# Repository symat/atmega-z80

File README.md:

ATMega-Z80
==========

We are building here yet another 8bit hobby computer. Because it is fun. And this is what an engineer does, *"MIDWAY upon the journey of our life"*. ;)

Disclaimer: **Use anything in this repo with caution!**

Nothing works yet, we just started to plan the whole thing. The only thing we are sure is that things will change, as we move forward. Plus the fact that we will move forward very slooowly, as this is only a hobby project and everyone is quite busy with other things. 

Table of Contents
-----------------

  * [Goals](#goals)
  * [Hardware design](#hardware-design)
    * [Schema](#schema)
    * [PCB](#pcb)
  * [Using the board](#using-the-board)
  * [Development](#development)
    * [Prerequisites for Linux](#prerequisites-for-linux)
    * [Prerequisites for Windows](#prerequisites-for-windows)
    * [Prerequisites for Mac](#prerequisites-for-mac)
    * [(Optional) Configuring USB HWID](#optional-configuring-usb-hwid)
	* [ATMega Programmer](#atmega-programmer)
	  * [Initializing ATMega clock](#initializing-atmega-clock)
	  * [Deploying the ATMega code](#deploying-the-atmega-code)
	* [Deploying the Z80 'ROM' code](#deploying-the-z80-rom-code)
  * [License](#license)

Goals
=====

**The main goals are:**

 - Using a well-known 8bit CPU.
 - Let's keep the HW design relatively simple. (I'm personally more interested in the 8bit programming part and want to go deeper into the kernel and user code.)
 - We should be able to compile C code to run it on the new computer.
 - We don't need a full-fledged, stand-alone computer. I'm sure everyone has already a few of those on our desks... We don't build this to actually use it for work or gaming.
 - The whole computer should not have more than a handful of ICs. No FPGA or complex MCU with a need for an expensive programmer. Anyone should be able to build it on a breadboard for $40-50 worth of components (incl. programmer). 
 - Don't use logic level (voltage) converters, keep everything e.g. on 5V or on 3.3V.
 - We can have VGA / keyboard / SD Card support later (if someone needs it), but the first thing is to have USB support and connection to a PC, so we can implement a small thin terminal program that can send keyboard and mouse events, display video, play music even.

Hardware design
===============

The basic design is not new or original, it is very much based on other projects available on the internet. I'm especially grateful for [this one, the MBC2 project](https://hackaday.io/project/159973-z80-mbc2-a-4-ics-homebrew-z80-computer) (80% of the HW design comes from this project). 

 - We use a relatively new Z80 CPU, capable to run at 10MHz.
 - A 20MHz ATMega chip (similar to those you can find in Arduino boards) is helping the CPU as ROM emulator, boot loader and clock generator. Also handling all the IO requests from the CPU.
 - An IO wait logic is implemented using an SR latch, forcing the CPU to wait until the ATMega chip processed the IO operations.
 - The ATMgega chip can access both the data bus and the first 4 bits of the address bus. Having access to a part of the address bus makes the boot loading easier and also enables us to use IO and interrupt addresses.
 - For now, we added 512 KB RAM, using 16 KB banks. The CPU will be able to set the bank ID with an IO write operation and then the given 16 KB bank will be visible for the CPU on the third 16KB memory slot of the 64KB address space (between 0x8000 and 0xbfff).
 - We store the bank address in an 8 bit gated D latch IC. This means we can address the banks in 8 bits, so the design works until 4 MB (16KB * 256). But 4MB sounds a bit overkill and also more expensive. It is hard to find a single DIP parallel 8bit SRAM chip over 512 KB. Moving away from DIP makes it harder to assemble the computer on a breadboard, while using many separate 512 KB RAM chips would require a bit more complex banking logic (with lot more footprint and wiring on the breadboard). But in theory we can extend the RAM later easily if needed.
 - We have an USB controller chip, converting the UART port of ATMega to USB.
 - The USB port is used also for powering the whole atmega-z80.
 - We have a user button and LED, both can be used by the programmer to interact directly with the user. (who needs 101 keys and zillion pixels... :p)
 - We plan to add some status indicator LEDs:
	 - Power LED (power come through the USB cable)
	 - Z80 running LED (means the Z80 is active, not in 'halt' state)
	 - USB IO LED (ATMega is communicating through the USB)
	 - CPU IO LED (the CPU is doing IO read or write)
	 - Memory LED (the CPU is reading from / writing to anywhere in the RAM)
	 - Extended memory LED (the CPU is reading from / writing to the banked part of the RAM)
	 - User LED (some program running on the Z80 turned the user LED on)

Schema
------
Please take a look here for the latest version: [schema/atmega-z80.pdf](schema/atmega-z80.pdf)

You can find the editable files in the ['schema' folder](schema/). We use the KICad tool for schema design: https://www.kicad.org/download/

PCB
---

TODO

Using the board
===============

For now, you can only interact with the board using the console application. Later we might add keyboard and display support as well as other periferias. But the console app should be always capable to emulate these, as people might not want to use dedicated periferias for ATMega-Z80.

Prerequisites to use the console:
```
pip3 install pyserial==3.5
```

Using the console:
```
src/console/console.py
```

Development
===========

The source code needs to be deployed into the ATMega chip can be found here: ['src/atmega' folder](src/atmega/)

The source code running on the Z80 can be found here: ['src/z80' folder](src/z80/)

The source code for the console app (running on the PC and connecting to the ATMega on USB): ['src/console' folder](src/z80/)

The console is mainly developed for end users, to interact with the ATMega (until we don't have keyboard and display support, or if the user don't want to buy/attch separate devices to the board). However, during development you can also use the console as a debugger and you can also upload Z80 code using the console. However, to deploy code running on the ATMega, you need to use a programmer (see: [here](#atmega-programmer) )

You can not use the console and the ATMega programmer in the same time. **Make sure you are disconnecting the USB port while you are using the programmer!**

Prerequisites for Linux
-----------------------

TODO

Prerequisites for Windows
-----------------------

TODO

Prerequisites for Mac
---------------------

First, make sure you have xcode command line developer tools installed with:
```
$ xcode-select --install
```

Then install the latest versions of the avr command line tools (avr-libc included in avr-gcc):
```
$ brew tap osx-cross/avr
$ brew install avr-gcc@11 avr-binutils avrdude
```
(you can check the current versions of avr-gcc available through homebrew here: https://github.com/osx-cross/homebrew-avr)

Add the following two lines to your .bash_profile or .zshrc file:
```
export PATH="/usr/local/opt/avr-gcc@11/bin:$PATH"
export AVRGCC_LDFLAGS="-L/usr/local/opt/avr-gcc@11/lib"
```

(Optional) Configuring USB HWID
-------------------------------

You can program the MCP2221A chip, setting the HWID (Vendor ID: 0x1209, Product ID: 0x80A0) of the USB device. We 'registered' an open USB HWID in [pid.codes](https://pid.codes/). This is not mandatory, you can also use the MCP2221A chip with factory default HWID, but in this case the console won't auto-detect the port and you need to select the correct port manually from a list each time you start the console.

**Prerequisites (python):**

```
pip3 install mcp2221==1.0.0
pip3 install hidapi==0.10.1
```

**Prerequisites (C lib):**

The mcp2221 python library is using the hidapi library, which got merged into libusb in 2019. So depending on the age of your OS, you might need to install libhidapi or libusb. 

For me on Mac with up-to-date homebrew, this worked: `brew install hidapi`

According to the project page (https://github.com/trezor/cython-hidapi) for linux this one should work at the moment:
`sudo apt-get install python-dev libusb-1.0-0-dev libudev-dev`

**Setting the HWID for the board**

Use the following command to set the Vendor ID, Product ID and Product Description on the board: `./src/console/program_hwid.py`

**Reseting the HWID**

Use the following command to reset the Vendor ID, Product ID and Product Description on the board to the MPC2221A factory defaults:  `./src/console/program_hwid.py --reset`

ATMega Programmer
-----------------

To update the code running on the ATMega, we are using the open source UABAsp programmer (https://www.fischl.de/usbasp/). It comes with an ISP 10 connector. You need to connect the programmer to the ATMega ports indicated in the schema (RESET and PB3, PB6, PB7). Also you need to connect the 5V and GND from the programmer to the board, basically using the Programmer as a power source while you are programing the board. You can not use the console and the ATMega programmer in the same time. **Make sure you are disconnecting the USB port while you are using the programmer!**

The following photo shows how to connect the ISP 10 connector to your breadboard:

### Initializing ATMega clock

ATMega shipped with internal 8MHz clock enabled and the clock prescaler set to 8, resulting in 1 MHz clock speed. In the code we assume you wired the 20 MHz crystal to ATMega already. To configure the external crystal oscillator to be used, you need to set the fuses on ATMega once before programming it. (useful online fuse bit calculator: http://eleccelerator.com/fusecalc/fusecalc.php?chip=atmega324pa)

**Make sure you are disconnecting the USB port while you are using the programmer to change the ATMega clock speed!**

You can set the fuses in ATMega to various clock speeds. We support the following speeds:
- 20MHz (the full speed of our external osciallator)
- 8 MHz (internal RC Oscillator)
- 2.5 MHz (dividing the external oscillator speed by 8)
- 1 MHz (internal RC Oscillator, divided by 8; this is the factory default for the ATMega chip)
- 128 KHz (using the internal ATMega slow oscillator - might be tricky, see the slow clock warning)
- 16 KHz (internal slow oscillator, divided by 8 - might be tricky, see the slow clock warning)

When you change the clock speed, you also need to change the MCU_SPEED parameter, to instruct the copmiler to use the proper speed. You need to run `cmake` and `make clean` and `make` to make sure your changes are taking effect. To test your settings, you can use the `make upload_blinky` to upload a program to ATMega which will blink the user led, once in each second. You can see the exact steps below.

```
# if you want to change the clock speed to: 20MHz
make atmega_fuse_init
cmake -DMCU_SPEED=20000000 .

# if you want to change the clock speed to: 8MHz
make atmega_fuse_init_8000khz
cmake -DMCU_SPEED=8000000 .

# if you want to change the clock speed to: 2.5MHz
make atmega_fuse_init_2500khz
cmake -DAVRDUDE_BIT_CLOCK=3 -DMCU_SPEED=2500000 .

# if you want to change the clock speed to: 1MHz (this is the factory default)
make atmega_fuse_factory_reset
cmake -DAVRDUDE_BIT_CLOCK=8 -DMCU_SPEED=1000000 .

# if you want to change the clock speed to: 128KHz (this can be a bit tricky, see the SLOW CLOCK WARNING above)
make atmega_fuse_init_128khz
cmake -DAVRDUDE_BIT_CLOCK=50 -DMCU_SPEED=128000 .

# if you want to change the clock speed to: 16KHz (this can be a bit tricky, see the SLOW CLOCK WARNING above)
make atmega_fuse_init_16khz
cmake -DAVRDUDE_BIT_CLOCK=200 -DMCU_SPEED=16000 .

# you need to rebuild the code with the new clock settings
make clean
make

# this command will make your user LED on the board to flash once in each second
# this way you can make sure the clock is set properly
# (you will have to re-deploy the original ATMega code after this step)
make upload_blinky
```

**!SLOW CLOCK WARNING!** (check this below, before you would try to use the slower clock options)

You might see the following error when you try to program the board, after you changed the clock speed to some slower option:
```
avrdude: error: program enable: target doesn't answer. 1 
avrdude: initialization failed, rc=-1
         Double check connections and try again, or use -F to override
         this check.

avrdude done.  Thank you.
```
The problem can be that the usbasp programmer is trying to talk 'too fast' with the ATMega chip on our board, if you set slow ATMega clocks. Normally you can use the `-B` option for avrdude to instruct the programmer to talk slower. This option can be provided through the AVRDUDE_BIT_CLOCK cmake parameter. I tested the various clock speeds with different AVRDUDE_BIT_CLOCK parameters, so the above examples should work. However, there is a chance that your programmer is different. If you see this error, then you can try to increase the bit clock for your programmer. Also, increasing the bit clock will make the programming slower. So you might want to find the ideal AVRDUDE_BIT_CLOCK for your programmer.

An other 'slow clock' problem you can face with usbasp programmer is that avrdude actually is unable to set the bit clock:
```
avrdude: warning: cannot set sck period. please check for usbasp firmware update.
```
Based on some googling, this happens when you have a very old usbasp programmer or if your programmer has some non-official usbasp frameware. In this case you either need to upgrade the programmer's firmware or you need to connect the 'slow clock' jumper on your programmer. This is JP1 on the original schematic of usbasp (https://www.fischl.de/usbasp/), while in case of my programmer, this was actually marked as JP3 (so be careful). If you choose the other option, the latest frameware can be downloaded from the usbasp site. However you will need to have a second programmer to be able to refresh the framework of your original programmer. (but I had to do this, as in my case even the 'slow clock' jumper was not enough after I set my ATMgit statusega to 16KHz)

Anyway, if you don't want to spend time on these 'slow clock' problems then you can simply skip using clock rates slower than 1 MHz.

### Deploying the ATMega code

Below it is shown how can you build the atmega code and flash it to ATMega. Note, the ATMega flash will not contain the Z80 'ROM code'. The Z80 code can be copied to ATMega by using the console app. **Make sure you are disconnecting the USB port while you are using the programmer!**
```
make clean
make
make upload_z80_prog_loader
```

You can run the tests for the ATMega program by: `python3 src/console/test_atmega_z80.py`
To run a single test named as "test_upload_z80_code_to_ram": `python3 src/console/test_atmega_z80.py --test ATMegaZ80Tests.test_upload_z80_code_to_ram`

Deploying the Z80 ROM code
--------------------------

The memory will be initialized on startup by the ATMega chip, copying the Z80 'ROM' into the memory from the ATMega flash. To update Z80 ROM, you don't need an AVR Programmer, you can use the console to uppload the new ROM file to ATMega.

```
TODO
```

License
=======
This is an open project. The software is licensed under BSD-3, while the hardware is licensed under CERN-OHL-P. Both licenses are permissive. Feel free to use anything here, just don't point fingers / blame us ;)

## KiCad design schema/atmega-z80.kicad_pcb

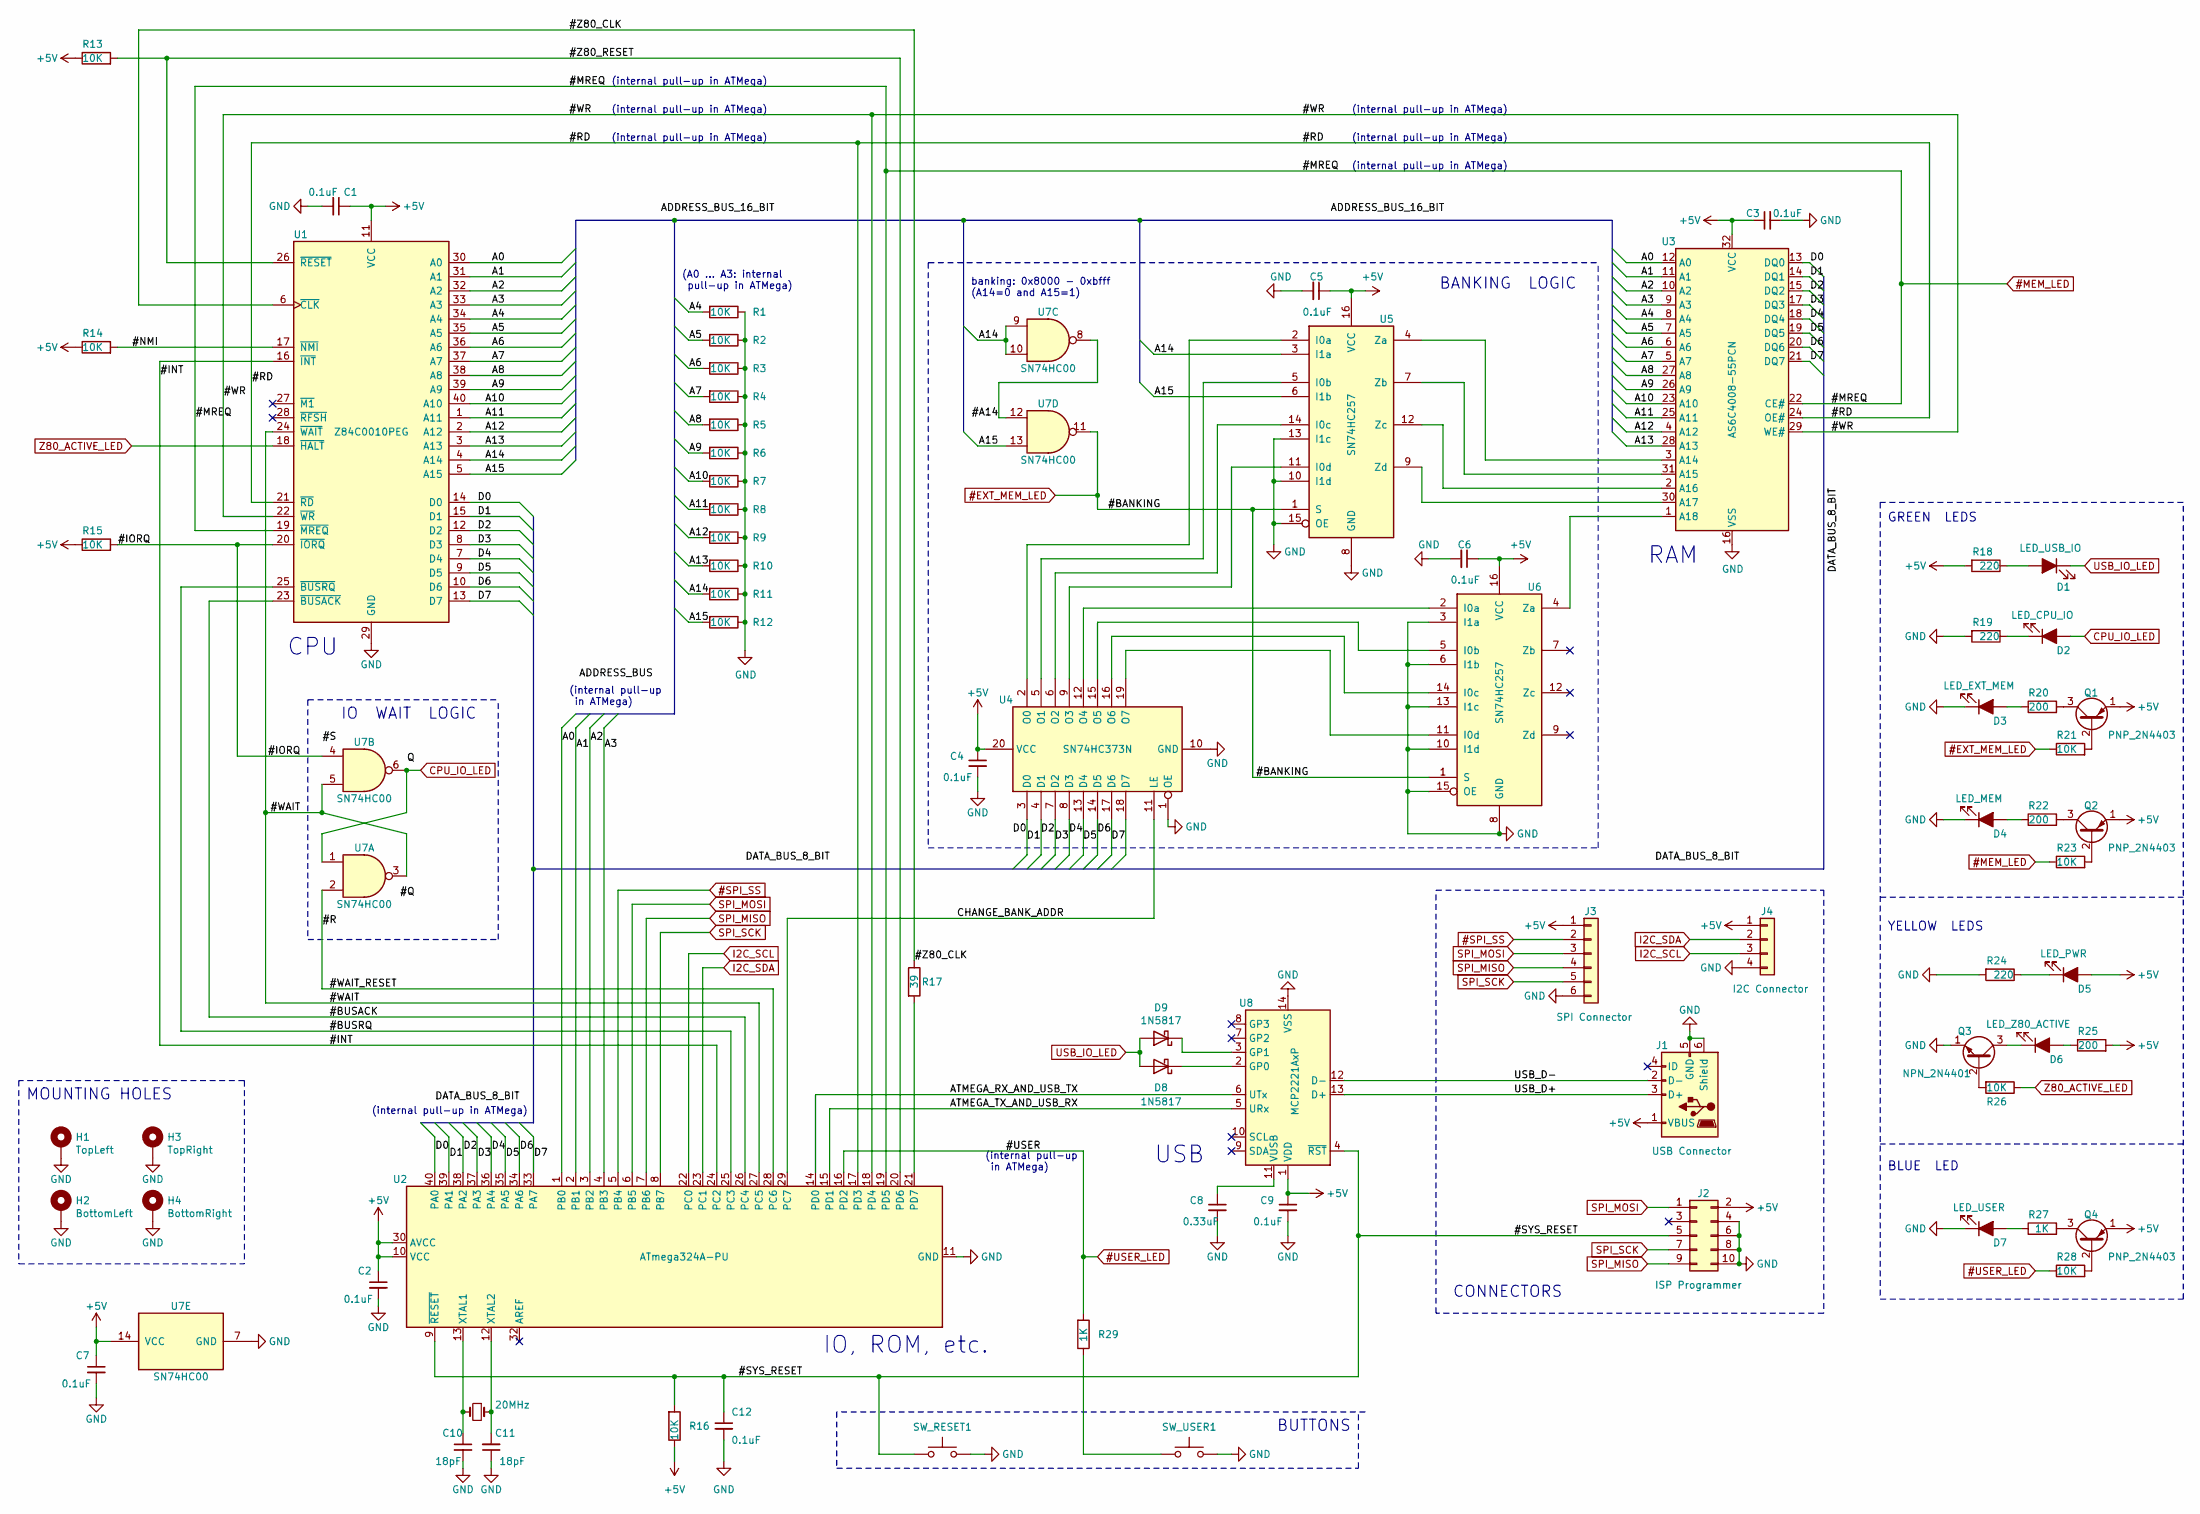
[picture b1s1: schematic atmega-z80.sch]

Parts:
C1, C2, C3, C4, C5, C6, C7, C9, C12: 0.1uF; C_1206_3216Metric_Pad1.33x1.80mm_HandSolder
C8: 0.33uF; C_1206_3216Metric_Pad1.33x1.80mm_HandSolder
C10, C11: 18pF; C_1206_3216Metric_Pad1.33x1.80mm_HandSolder
D1: LED_USB_IO; LED_D5.0mm
D2: LED_CPU_IO; LED_D5.0mm
D3: LED_EXT_MEM; LED_D5.0mm
D4: LED_MEM; LED_D5.0mm
D5: LED_PWR; LED_D5.0mm
D6: LED_Z80_ACTIVE; LED_D5.0mm
D7: LED_USER; LED_D5.0mm
D8, D9: 1N5817; D_DO-41_SOD81_P10.16mm_Horizontal
H1: TopLeft; MountingHole_2.2mm_M2_DIN965_Pad
H2: BottomLeft; MountingHole_2.2mm_M2_DIN965_Pad
H3: TopRight; MountingHole_2.2mm_M2_DIN965_Pad
H4: BottomRight; MountingHole_2.2mm_M2_DIN965_Pad
J1: USB Connector; USB_Mini-B_Molex-54819-0519
J2: ISP Programmer; PinHeader_2x05_P2.54mm_Vertical
J3: SPI Connector; PinHeader_1x06_P2.54mm_Vertical
J4: I2C Connector; PinHeader_1x04_P2.54mm_Vertical
Q1, Q2, Q4: PNP_2N4403; TO-92_Inline
Q3: NPN_2N4401; TO-92_Inline_Wide
R1, R2, R3, R4, R5, R6, R7, R8, R9, R10, R11, R12, R13, R14, R15, R16, R21, R23, R26, R28: 10K; R_1206_3216Metric_Pad1.30x1.75mm_HandSolder
R17: 39; R_1206_3216Metric_Pad1.30x1.75mm_HandSolder
R18, R19, R24: 220; R_1206_3216Metric_Pad1.30x1.75mm_HandSolder
R20, R22, R25: 200; R_1206_3216Metric_Pad1.30x1.75mm_HandSolder
R27, R29: 1K; R_1206_3216Metric_Pad1.30x1.75mm_HandSolder
SW_RESET1: RESET; SW_PUSH_6mm_H5mm
SW_USER1: USER; SW_PUSH_6mm_H5mm
U1: Z84C0010PEG; DIP-40_W15.24mm_Socket
U2: ATmega324A-PU; DIP-40_W15.24mm_Socket
U3: AS6C4008-55PCN; DIP-32_W15.24mm_Socket
U4: SN74HC373N; DIP-20_W7.62mm_Socket
U5, U6: SN74HC257; DIP-16_W7.62mm_Socket
U7: SN74HC00; DIP-14_W7.62mm_Socket
U8: MCP2221AxP; DIP-14_W7.62mm_Socket
Y1: 20MHz; Crystal_HC49-U_Vertical

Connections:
#EXT_MEM_LED: R21.1, U5.1 (S), U6.1 (S), U7.11
#MEM_LED: R23.1, U1.19 (~MREQ~), U2.19 (PD5), U3.22 (CE#)
#SPI_SS: J3.2, U2.5 (PB4)
#USER_LED: R28.1, R29.2, U2.16 (PD2)
+5V: C1.1, C2.1, C3.1, C4.1, C5.1, C6.1, C7.1, C9.1, D5.2 (A), J1.1 (VBUS), J2.2, J3.1, J4.1, Q1.1 (E), Q2.1 (E), Q4.1 (E), R13.1, R14.1, R15.1, R16.1, R18.2, R25.2, U1.11 (VCC), U2.10 (VCC), U2.30 (AVCC), U3.32 (VCC), U4.20 (VCC), U5.16 (VCC), U6.16 (VCC), U7.14 (VCC), U8.1 (VDD)
/#A14: U7.8, U7.12
/#BUSACK: U1.23 (~BUSACK~), U2.26 (PC4)
/#BUSRQ: U1.25 (~BUSRQ~), U2.25 (PC3)
/#INT: U1.16 (~INT~), U2.24 (PC2)
/#IORQ: R15.2, U1.20 (~IORQ~), U7.4
/#NMI: R14.2, U1.17 (~NMI~)
/#R: U2.28 (PC6), U7.2
/#RD: U1.21 (~RD~), U2.17 (PD3), U3.24 (OE#)
/#SYS_RESET: C12.1, J2.5, R16.2, SW_RESET1.2, U2.9 (~RESET), U8.4 (~RST)
/#WAIT: U1.24 (~WAIT~), U2.27 (PC5), U7.3, U7.5
/#WR: U1.22 (~WR~), U2.18 (PD4), U3.29 (WE#)
/#Z80_CLK: R17.1, U1.6 (~CLK~)
/#Z80_RESET: R13.2, U1.26 (~RESET~), U2.20 (PD6)
/A0: U1.30 (A0), U2.1 (PB0), U3.12 (A0)
/A1: U1.31 (A1), U2.2 (PB1), U3.11 (A1)
/A2: U1.32 (A2), U2.3 (PB2), U3.10 (A2)
/A3: U1.33 (A3), U2.4 (PB3), U3.9 (A3)
/A4: R1.2, U1.34 (A4), U3.8 (A4)
/A5: R2.2, U1.35 (A5), U3.7 (A5)
/A6: R3.2, U1.36 (A6), U3.6 (A6)
/A7: R4.2, U1.37 (A7), U3.5 (A7)
/A8: R5.2, U1.38 (A8), U3.27 (A8)
/A9: R6.2, U1.39 (A9), U3.26 (A9)
/A10: R7.2, U1.40 (A10), U3.23 (A10)
/A11: R8.2, U1.1 (A11), U3.25 (A11)
/A12: R9.2, U1.2 (A12), U3.4 (A12)
/A13: R10.2, U1.3 (A13), U3.28 (A13)
/A14: R11.2, U1.4 (A14), U5.3 (I1a), U7.9, U7.10
/A15: R12.2, U1.5 (A15), U5.6 (I1b), U7.13
/ATMEGA_RX_AND_USB_TX: U2.14 (PD0), U8.6 (UTx)
/ATMEGA_TX_AND_USB_RX: U2.15 (PD1), U8.5 (URx)
/CHANGE_BANK_ADDR: U2.29 (PC7), U4.11 (LE)
/D0: U1.14 (D0), U2.40 (PA0), U3.13 (DQ0), U4.3 (D0)
/D1: U1.15 (D1), U2.39 (PA1), U3.14 (DQ1), U4.4 (D1)
/D2: U1.12 (D2), U2.38 (PA2), U3.15 (DQ2), U4.7 (D2)
/D3: U1.8 (D3), U2.37 (PA3), U3.17 (DQ3), U4.8 (D3)
/D4: U1.7 (D4), U2.36 (PA4), U3.18 (DQ4), U4.13 (D4)
/D5: U1.9 (D5), U2.35 (PA5), U3.19 (DQ5), U4.14 (D5)
/D6: U1.10 (D6), U2.34 (PA6), U3.20 (DQ6), U4.17 (D6)
/D7: U1.13 (D7), U2.33 (PA7), U3.21 (DQ7), U4.18 (D7)
/USB_D+: J1.3 (D+), U8.13 (D+)
/USB_D-: J1.2 (D-), U8.12 (D-)
CPU_IO_LED: D2.2 (A), U7.1, U7.6
GND: C1.2, C2.2, C3.2, C4.2, C5.2, C6.2, C7.2, C8.2, C9.2, C10.2, C11.1, C12.2, D3.1 (K), D4.1 (K), D7.1 (K), H1.1, H2.1, H3.1, H4.1, J1.5 (GND), J1.6 (Shield), J2.4, J2.6, J2.8, J2.10, J3.6, J4.4, Q3.1 (E), R1.1, R2.1, R3.1, R4.1, R5.1, R6.1, R7.1, R8.1, R9.1, R10.1, R11.1, R12.1, R19.2, R24.2, SW_RESET1.1, SW_USER1.2, U1.29 (GND), U2.11 (GND), U2.31 (GND), U3.16 (VSS), U4.1 (OE), U4.10 (GND), U5.8 (GND), U5.10 (I1d), U5.13 (I1c), U5.15 (OE), U6.3 (I1a), U6.6 (I1b), U6.8 (GND), U6.10 (I1d), U6.13 (I1c), U6.15 (OE), U7.7 (GND), U8.14 (VSS)
I2C_SCL: J4.3, U2.22 (PC0)
I2C_SDA: J4.2, U2.23 (PC1)
unnamed: C8.1, U8.11 (VUSB)
unnamed: C10.1, U2.13 (XTAL1), Y1.2
unnamed: C11.2, U2.12 (XTAL2), Y1.1
unnamed: D1.2 (A), R18.1
unnamed: D2.1 (K), R19.1
unnamed: D3.2 (A), R20.1
unnamed: D4.2 (A), R22.1
unnamed: D5.1 (K), R24.1
unnamed: D6.1 (K), Q3.3 (C)
unnamed: D6.2 (A), R25.1
unnamed: D7.2 (A), R27.1
unnamed: D8.1 (K), U8.2 (GP0)
unnamed: D9.1 (K), U8.3 (GP1)
unnamed: Q1.2 (B), R21.2
unnamed: Q1.3 (C), R20.2
unnamed: Q2.2 (B), R23.2
unnamed: Q2.3 (C), R22.2
unnamed: Q3.2 (B), R26.2
unnamed: Q4.2 (B), R28.2
unnamed: Q4.3 (C), R27.2
unnamed: R17.2, U2.21 (PD7)
unnamed: R29.1, SW_USER1.1
unnamed: U3.1 (A18), U6.4 (Za)
unnamed: U3.2 (A16), U5.12 (Zc)
unnamed: U3.3 (A14), U5.4 (Za)
unnamed: U3.30 (A17), U5.9 (Zd)
unnamed: U3.31 (A15), U5.7 (Zb)
unnamed: U4.2 (O0), U5.2 (I0a)
unnamed: U4.5 (O1), U5.5 (I0b)
unnamed: U4.6 (O2), U5.14 (I0c)
unnamed: U4.9 (O3), U5.11 (I0d)
unnamed: U4.12 (O4), U6.2 (I0a)
unnamed: U4.15 (O5), U6.5 (I0b)
unnamed: U4.16 (O6), U6.14 (I0c)
unnamed: U4.19 (O7), U6.11 (I0d)
SPI_MISO: J2.9, J3.4, U2.7 (PB6)
SPI_MOSI: J2.1, J3.3, U2.6 (PB5)
SPI_SCK: J2.7, J3.5, U2.8 (PB7)
USB_IO_LED: D1.1 (K), D8.2 (A), D9.2 (A)
Z80_ACTIVE_LED: R26.1, U1.18 (~HALT~)

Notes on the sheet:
BUTTONS
CONNECTORS
IO WAIT LOGIC
CPU
IO, ROM, etc.
RAM
BANKING LOGIC
YELLOW LEDS
GREEN LEDS
BLUE LED
(internal pull-up in ATMega)
(A0 … A3: internal pull-up in ATMega)
banking: 0x8000 - 0xbfff (A14=0 and A15=1)
USB
(internal pull-up in ATMega)
MOUNTING HOLES

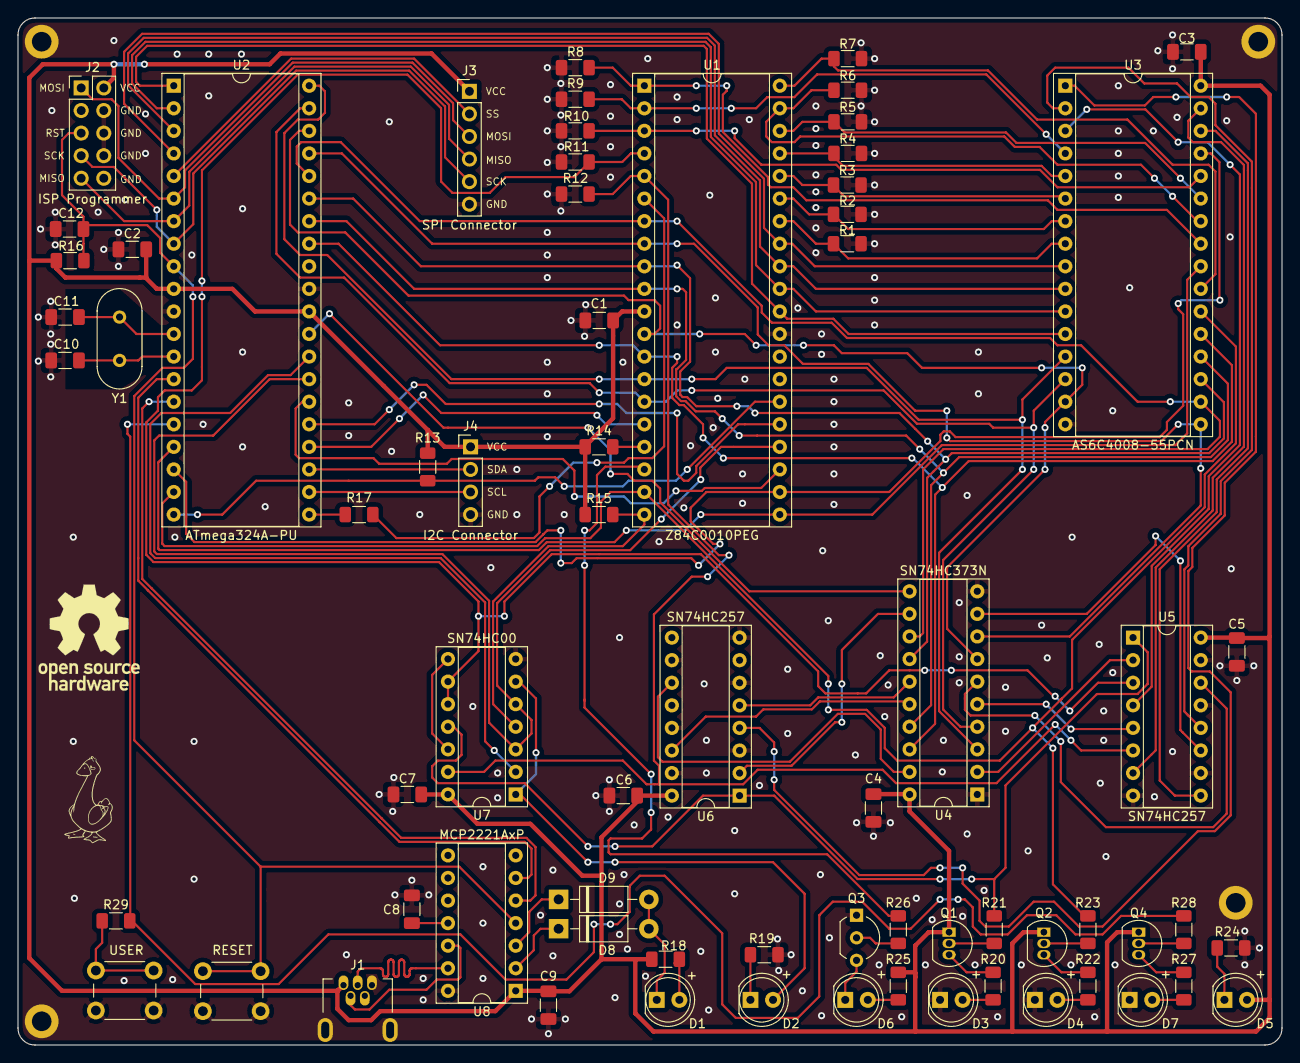
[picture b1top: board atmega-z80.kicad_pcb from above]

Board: 2 copper layers, 142.2 x 115.6 mm, 73 parts (0 on the bottom side), 91 nets.

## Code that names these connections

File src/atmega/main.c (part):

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    /*
     *  SIG1 group
     *
     *  PC0 - I2C SCL (input, pull-up)
     *  PC1 - I2C SDA (input, pull-up)
     *  PC2 - #INT line (output, high)
     *  PC3 - #BUSRQ line (output, high)
     *  PC4 - #BUSACK line (input, no pull-up)
     *  PC5 - #WAIT line (input, no pull-up)
     *  PC6 - #WAIT_RESET line (output, high)
     *  PC7 - CHANGE_BANK_ADDR line (output, low)
     */
    DDR_SIG1 = 0b11001100;
    PORT_SIG1 = 0b01001111;
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    /*
     *  SIG2 group
     *
     *  PD0 - USART RxD (input, pull-up)
     *  PD1 - USART TxD (output, high)
     *  PD2 - User switch (input, pull-up)
     *  PD3 - #RD (input, pull-up)
     *  PD4 - #WR (input, pull-up)
     *  PD5 - #MREQ (input, pull-up)
     *  PD6 - #RESET (output, low)
     *  PD7 - #CLK (output, high)
     */
    DDR_SIG2 = 0b11000010;
    PORT_SIG2 = 0b10111111;
}

static void blink(int blinks) {
    DDRD |= (1<<2);        // set USER LED pin PD2 to output
    for (int i=0; i<blinks; i++) {
        PORTD &= ~(1<<2);  // drive USER LED pin PD2 low (light on)
        _delay_ms(500);    // delay 500 ms
        PORTD |= (1<<2);   // drive USER LED pin PD2 high (light off)
        _delay_ms(500);    // delay 500 ms
    }
}
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
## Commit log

2021-09-01 initial HW schema; update readme
2021-09-01 improve readme
2021-09-02 fix banking logic
2021-09-02 todo list for the schema
2021-09-05 schema v0.1 - using multiplexers plus some fixes
2021-09-05 schema v0.2 - reduce the number of resistors
2021-09-06 minor changes in schema and readme, nothing functional
2021-09-07 added PCB footprints, changed ISP connector
2021-09-07 update LED resistors
2021-09-10 hello world: blinking user led using 20MHz clock
2021-09-12 adding I2C connector and other fixes
2021-09-13 improving USB IO LED
2021-09-14 Preliminary PCB layout
2021-09-17 set USB hardware ID; autodetect the board; update readme
2021-09-18 add hardware license
2021-09-19 Reversed all diodes on line USB_IO_LED because GP0 and GP1 of U8 are active low. More PCB layout stuff.
2021-09-19 Reversed all diodes on line USB_IO_LED because GP0 and GP1 of U8 are active low. (#4)
    More PCB layout stuff.
2021-09-19 update schema version/date/licenses, generate pdf
2021-09-23 A bunch of improvements / additions - PCB layout improvements - 1N5817 diode datasheet - CMake support - ATMega program loader firmware - program loader tool (z80_prog_loader.py) - Z80 bootloader (bo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
2021-09-24 z80_prog_loader bugfixes - use BUSRQ signal to cleanly release the data bus after an IO request from Z80 - use memory bank 2 as default instead of 0 which would duplicate memory range [0x0000 - 0x3ff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
2021-09-25 z80_prog_loader small bugfixes and readability changes
2021-09-26 z80_prog_loader upload chunk size bugfix
2021-09-27 A bunch of improvements / additions (#5)
    * A bunch of improvements / additions
    - PCB layout improvements
    - 1N5817 diode datasheet
    - CMake support
    - ATMega program loader firmware
    - program loader tool (z80_prog_loader.py)
2021-09-27 abandoned changes
2021-09-29 z80_prog_loader console output and memory banking support memory banking logic bugfix z80 hello world sample
2021-09-29 Changed #Z80_RESET line pull-down (R13) to pull-up
2021-09-29 Switched to Pasmo assembler
2021-09-29 Added console output handling to z80_prog_loader.py
2021-10-02 PCB routing complete Minor improvements
2021-10-03 PCB routing and Pasmo switch (#6)
    * z80_prog_loader console output and memory banking support
    memory banking logic bugfix
    z80 hello world sample
    * Changed #Z80_RESET line pull-down (R13) to pull-up
    * Switched to Pasmo assembler
    * Added console output handling to z80_prog_loader.py
2021-10-06 Moved USB-mini connector to the left to prevent crossing of VDD and USB data lines.
2021-10-06 Added USART timeout checks
2021-10-08 Small USART code readability changes
2021-10-08 Added error and command codes to z80_prog_loader
2021-10-08 Added some more ground vias to PCB
2021-10-08 Updated atmega-z80.pdf
2021-10-15 Added mcp2221 python library implementation
2021-10-15 Fixed indexing bug in z80_prog_loader.py
2021-10-15 Fixed blink timing in blinky.asm
2021-10-16 Improvements and bugfixes (#7)
    Small improvements and bugfixes
    - USART timeout checks during Z80 code upload
    - error codes are now returned during Z80 code upload instead of a single ACK/NACK
    - added own implementation of mcp2221 python library due to a bug in the official one
    - updated atmega-z80.pdf
    - minor PCB improvements
2021-11-04 Support for multiple clock speed options + documentation
    CMake now supports to setup the following ATMega clock speeds:
    - 20MHz (the full speed of our external osciallator)
    - 8 MHz (internal RC Oscillator)
    - 2.5 MHz (dividing the external oscillator speed by 8)
    - 1 MHz (internal RC Oscillator, divided by 8; this is the factory default for the ATMega chip)
    - 128 KHz (using the internal ATMega slow oscillator - might be tricky, see the slow clock warning)
2021-11-05 32KHz is actually 16KHz
2021-11-05 ignore files generated by CMake
2021-11-05 fix in readme
2021-12-17 Support for multiple clock speed options + documentation (#8)
    * Support for multiple clock speed options + documentation
    CMake now supports to setup the following ATMega clock speeds:
    - 20MHz (the full speed of our external osciallator)
    - 8 MHz (internal RC Oscillator)
    - 2.5 MHz (dividing the external oscillator speed by 8)
    - 1 MHz (internal RC Oscillator, divided by 8; this is the factory default for the ATMega chip)
2021-12-17 ignore files generated by CMake (#9)
2022-12-16 state on 2022-12-16

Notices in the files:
schema/atmega-z80.sch:
Open project, licensed under BSD-3 and CERN-OHL-P.
